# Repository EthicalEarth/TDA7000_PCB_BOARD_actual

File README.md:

# TDA7000_PCB_BOARDP_actual

# This project is hight quality FM radio receiver.
RADIO 80-125Mhz with maximal frequency 130 Mhz, Kicad project

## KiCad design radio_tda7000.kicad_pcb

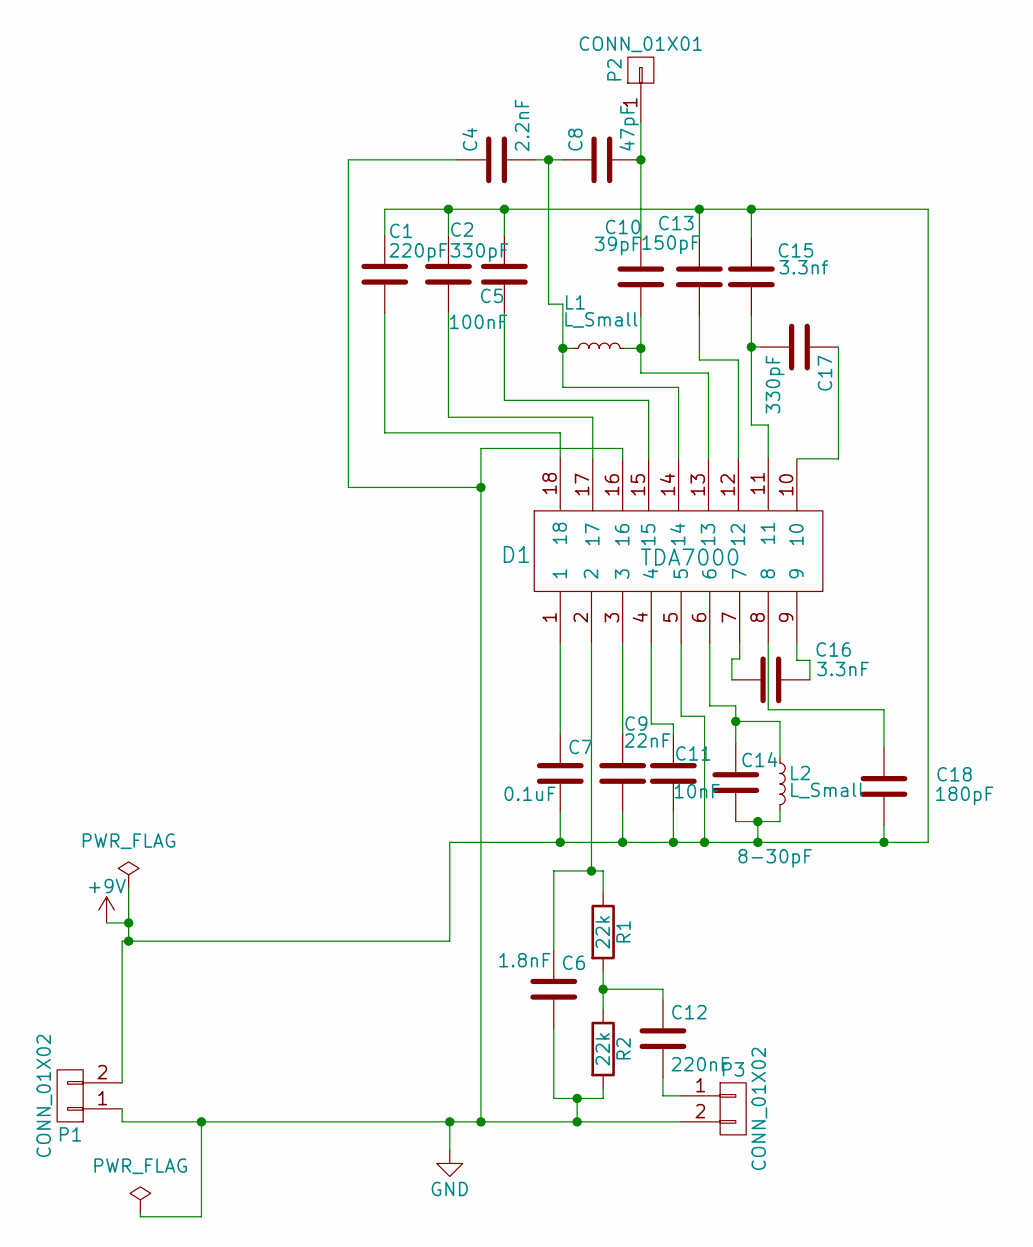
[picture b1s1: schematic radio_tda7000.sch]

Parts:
C1: 220pF; C_Disc_D4.3mm_W1.9mm_P5.00mm
C2, C17: 330pF; C_Disc_D4.3mm_W1.9mm_P5.00mm
C4: 2.2nF; C_Disc_D4.3mm_W1.9mm_P5.00mm
C5: 100nF; C_Disc_D7.5mm_W5.0mm_P7.50mm
C6: 1.8nF; C_Disc_D6.0mm_W2.5mm_P5.00mm
C7: 0.1uF; C_Disc_D4.3mm_W1.9mm_P5.00mm
C8: 47pF; C_Disc_D4.3mm_W1.9mm_P5.00mm
C9: 22nF; C_Disc_D4.3mm_W1.9mm_P5.00mm
C10: 39pF; C_Disc_D4.3mm_W1.9mm_P5.00mm
C11: 10nF; C_Disc_D4.3mm_W1.9mm_P5.00mm
C12: 220nF; C_Disc_D7.5mm_W5.0mm_P7.50mm
C13: 150pF; C_Disc_D4.3mm_W1.9mm_P5.00mm
C14: 8-30pF; C_Disc_D6.0mm_W2.5mm_P5.00mm
C15: 3.3nf; C_Disc_D4.3mm_W1.9mm_P5.00mm
C16: 3.3nF; C_Disc_D6.0mm_W4.4mm_P5.00mm
C18: 180pF; C_Disc_D7.5mm_W5.0mm_P7.50mm
D1: TDA7000; DIP-18_W7.62mm_LongPads
L1, L2: L_Small; Neosid_Inductor_Sd12k-style3
P1, P3: CONN_01X02; PINHEAD1-2
P2: CONN_01X01; Pin_Header_Straight_1x01
R1, R2: 22k; Resistor_Vertical_RM5mm

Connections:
+9V: C1.1, C2.1, C5.1, C7.2, C9.2, C11.2, C13.1, C14.2, C15.1, C18.2, D1.5, L2.2, P1.2
GND: C4.1, C6.2, D1.16, P1.1, P3.2, R2.2
unnamed: C1.2, D1.18
unnamed: C2.2, D1.17
unnamed: C4.2, C8.1, D1.14, L1.1
unnamed: C5.2, D1.15
unnamed: C6.1, D1.2, R1.1
unnamed: C7.1, D1.1
unnamed: C9.1, D1.3
unnamed: C8.2, C10.1, P2.1
unnamed: C10.2, D1.13, L1.2
unnamed: C11.1, D1.4
unnamed: C12.1, R1.2, R2.1
unnamed: C12.2, P3.1
unnamed: C13.2, D1.12
unnamed: C14.1, D1.6, L2.1
unnamed: C15.2, C17.2, D1.11
unnamed: C16.1, D1.9
unnamed: C16.2, D1.7
unnamed: C17.1, D1.10
unnamed: C18.1, D1.8

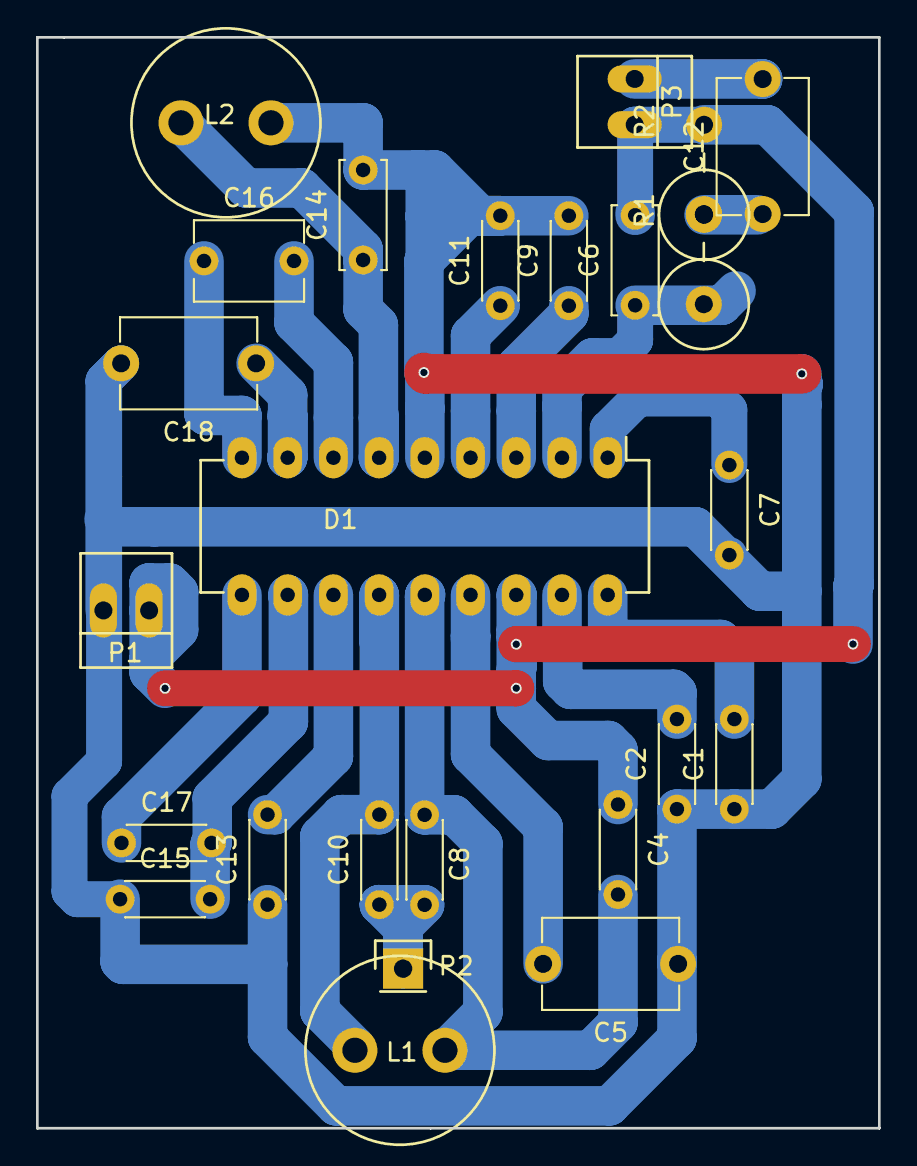
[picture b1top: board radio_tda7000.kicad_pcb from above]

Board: 2 copper layers, 46.8 x 60.6 mm, 25 parts (0 on the bottom side), 21 nets.

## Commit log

2018-07-28 Init
